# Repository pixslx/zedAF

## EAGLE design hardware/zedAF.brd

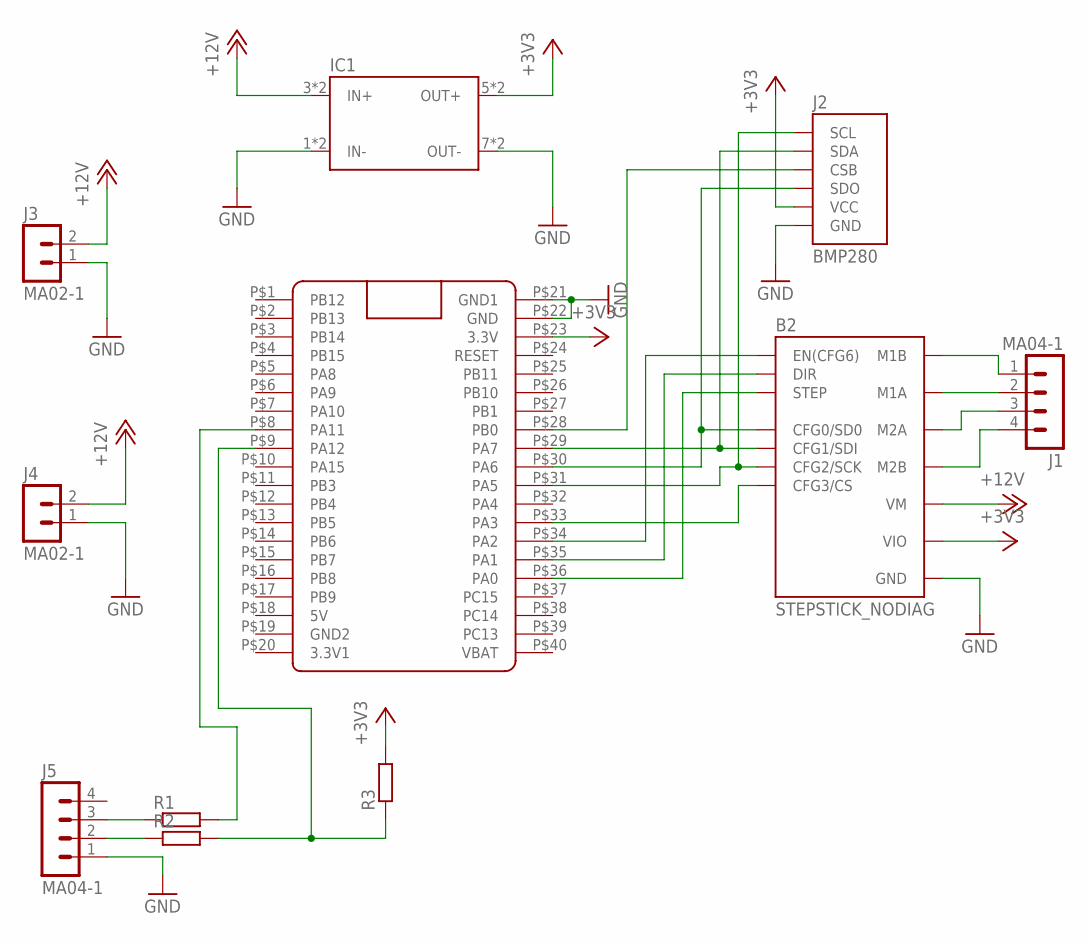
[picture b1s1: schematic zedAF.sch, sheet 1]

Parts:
B2: STEPSTICK_NODIAG; STEPSTICK
IC1: DC/DCDC; DC/DC
J1, J5: MA04-1
J2: BMP280; BMP280-1X6
J3, J4: MA02-1
R1, R2, R3: R-EU_R1206; R1206
U$1: BLUE_PILLWIDE; BLUE_PILL_WIDE

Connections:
+3V3: B2.VIO, IC1.5 (OUT+), IC1.6 (OUT+), J2.1 (VCC), R3.2, U$1.P$23 (3.3V)
+12V: B2.VM, IC1.3 (IN+), IC1.4 (IN+), J3.2, J4.2
GND: B2.GND@1 (GND), B2.GND@2 (GND), IC1.1 (IN-), IC1.2 (IN-), IC1.7 (OUT-), IC1.8 (OUT-), J2.2 (GND), J3.1, J4.1, J5.1, U$1.P$21 (GND1), U$1.P$22 (GND)
unnamed: B2.M1B, J1.1
unnamed: B2.M1A, J1.2
unnamed: B2.M2A, J1.3
unnamed: B2.M2B, J1.4
unnamed: B2.CFG1 (CFG1/SDI), J2.4 (SDA), U$1.P$29 (PA7)
unnamed: B2.NC/CFG0 (CFG0/SD0), J2.6 (SDO), U$1.P$30 (PA6)
unnamed: B2.CFG2 (CFG2/SCK), J2.3 (SCL), U$1.P$31 (PA5)
unnamed: B2.CFG3 (CFG3/CS), U$1.P$33 (PA3)
unnamed: B2.EN (EN(CFG6)), U$1.P$34 (PA2)
unnamed: B2.DIR, U$1.P$35 (PA1)
unnamed: B2.STEP, U$1.P$36 (PA0)
unnamed: J2.5 (CSB), U$1.P$28 (PB0)
unnamed: J5.3, R1.1
unnamed: J5.2, R2.1
unnamed: R2.2, R3.1, U$1.P$9 (PA12)
unnamed: R1.2, U$1.P$8 (PA11)

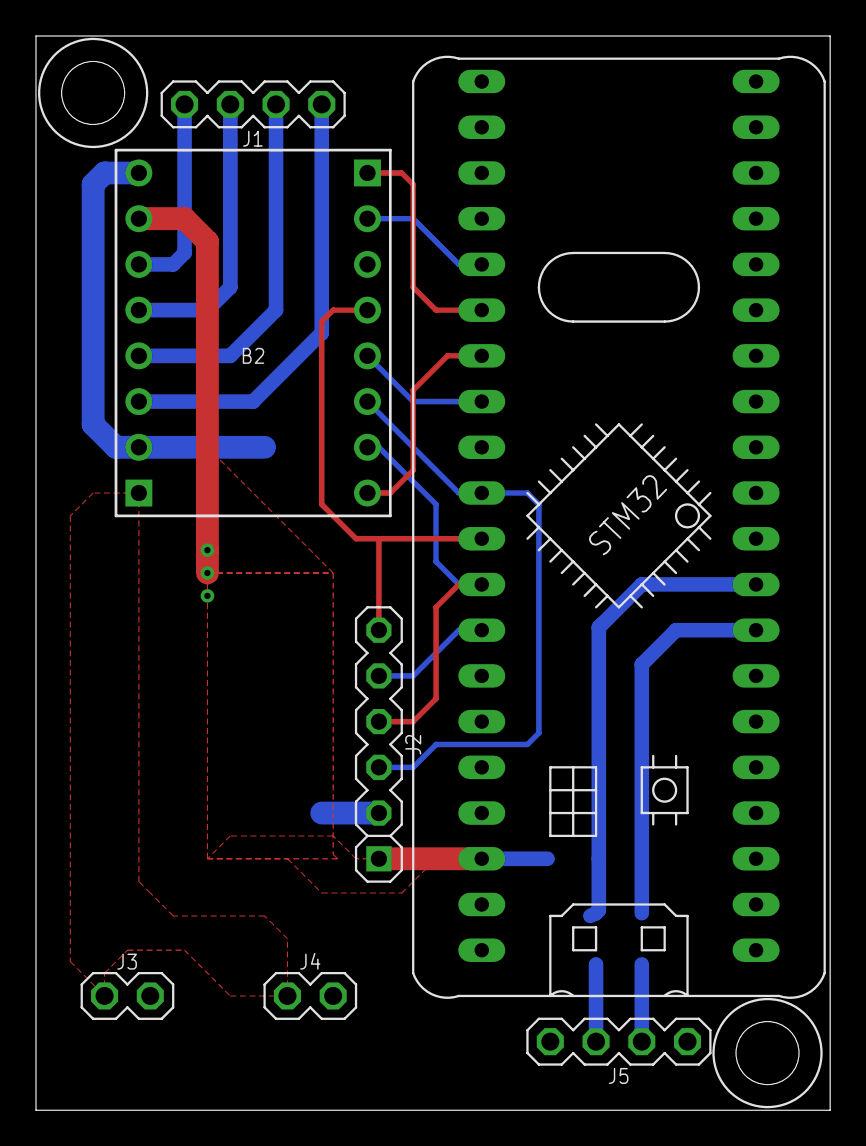
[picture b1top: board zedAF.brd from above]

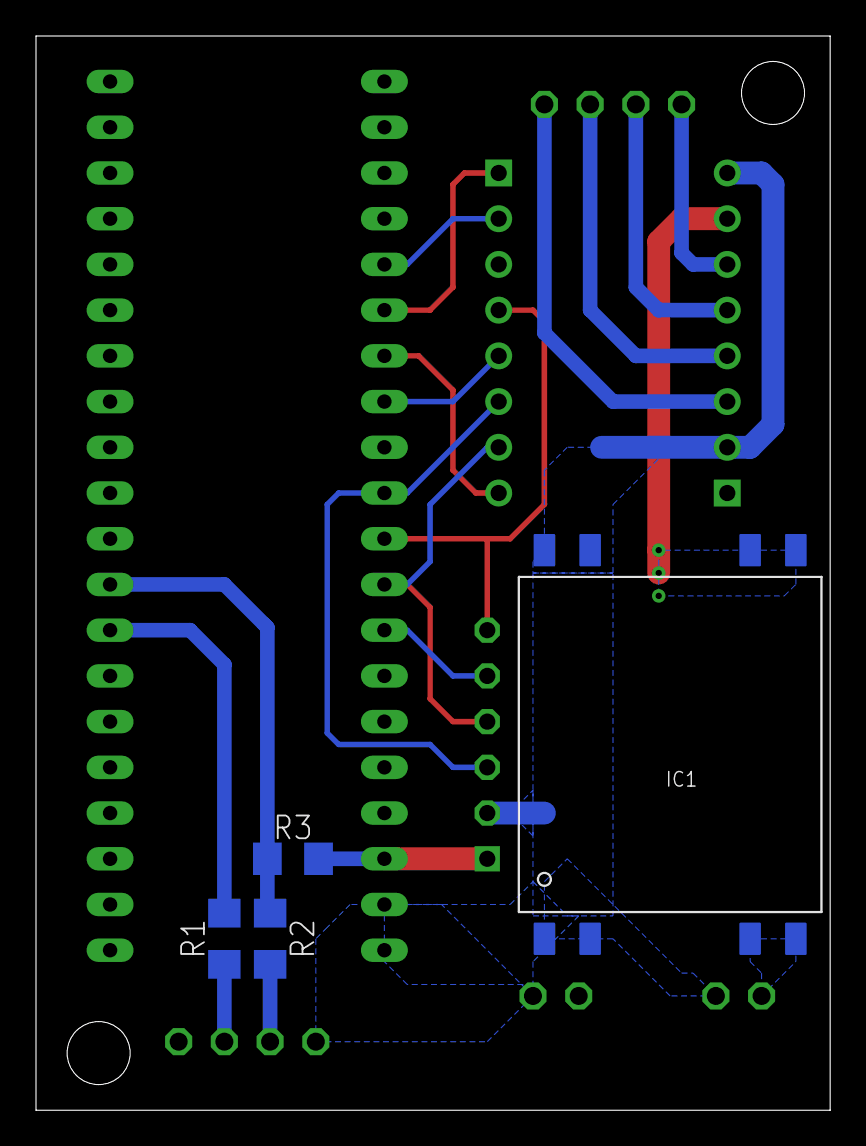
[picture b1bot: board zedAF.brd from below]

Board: 2 copper layers, 44.1 x 59.7 mm, 11 parts (4 on the bottom side), 19 nets.

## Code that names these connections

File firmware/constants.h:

#pragma once

#define SD_EN_PIN PA0
#define SD_DIR_PIN PA1
#define SD_STEP_PIN PA2
#define SD_CS_PIN PA3

#define BMP_CS_PIN PB10

const String VERSION = "11";

const long SERIAL_BOUD_RATE = 115200;

const double MAX_SPEED = 1000.0;
const int INITIAL_SPEED_DIVIDER = 2;
const double ACCELERATION = 200.0;
const bool INITIAL_HALF_STEP = false;
const int FULL_STEP_MICROSTEPS = 8;
const bool INITIAL_TEMP_COMPENSATION = false;
const int INWARD_DIRECTION = 1;
const int OUTWARD_DIRECTION = 0;

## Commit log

2019-09-07 corrected typo
